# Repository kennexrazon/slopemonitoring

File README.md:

# slopemonitoring
Schematic , Board and SketchUp Files (sch,brd,skp files)

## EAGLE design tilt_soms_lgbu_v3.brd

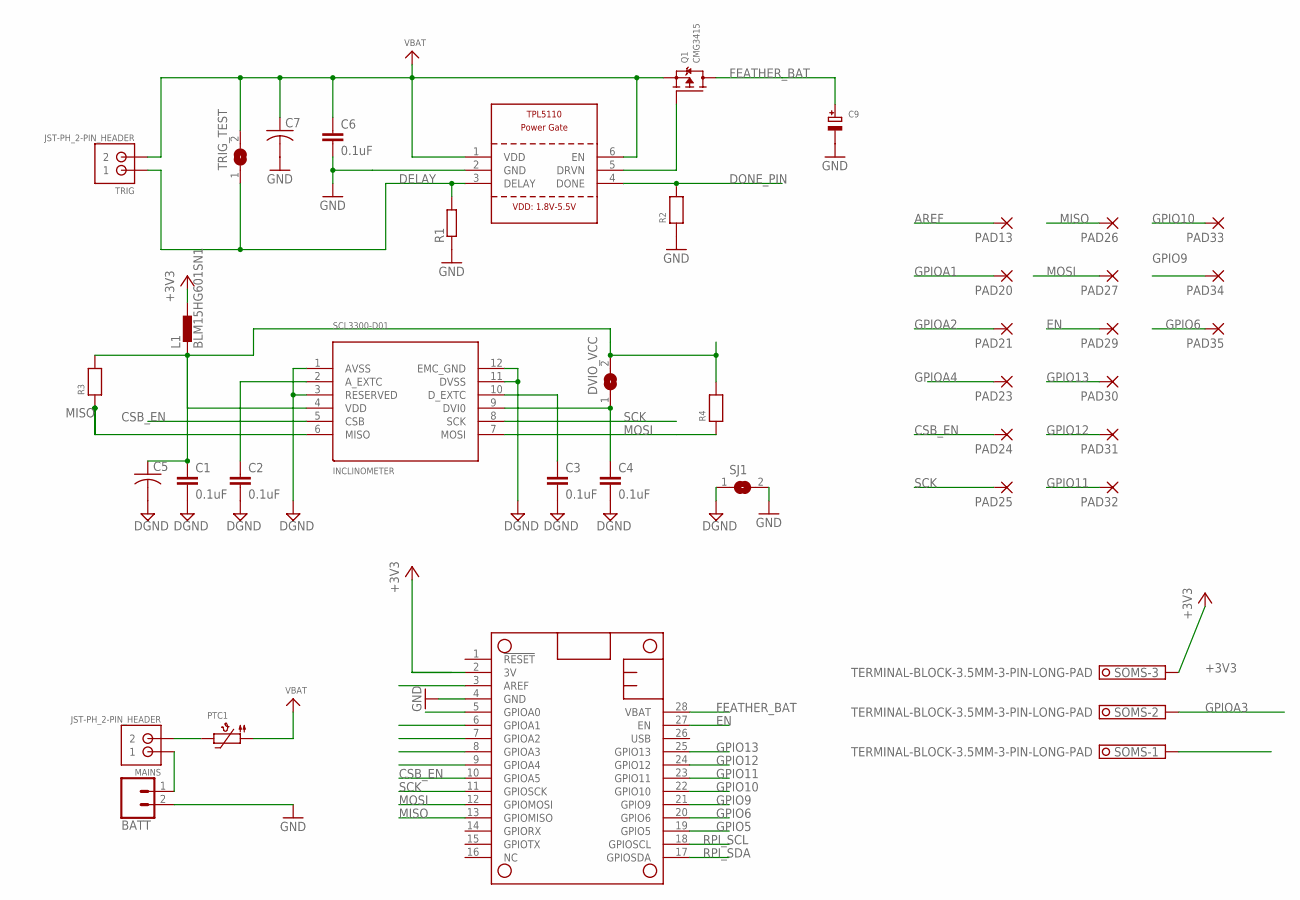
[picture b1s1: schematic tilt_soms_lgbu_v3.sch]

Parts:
BATT: CONN_02POLAR_LOCK; MOLEX-1X2_LOCK
C1, C2, C3, C4, C6: 0.1uF; C0402
C5, C7: C-USC1206K; C1206K
C9: CAP_TANTALUMA/3216_WAVE; EIA3216-18/A-W
DVIO_VCC: SOLDERJUMPER; SOLDERJUMPER_ARROW_NOPASTE
INCLINOMETER: SCL3300-D01
L1: BLM15HG601SN1; 0402
MAINS: JST-PH_2-PIN_HEADER; JST_B2B-PH_HEADER
MS2: FEATHERWINGFEATHERWING_EDC; FEATHERWING_NODIM_HOLES_2
PAD13, PAD20, PAD21, PAD23, PAD24, PAD25, PAD26, PAD27, PAD29, PAD30, PAD31, PAD32, PAD33, PAD34, PAD35: WIREPADSMD1,27-254; SMD1,27-2,54
PTC1: PTC1210
Q1: CMG3415; SOT23-WIDE
R1: R-EU_0207/10; 0207/10
R2, R3, R4: RESISTOR0805; 0805
SJ1: SJ
SOMS: TERMINAL-BLOCK-3.5MM-3-PIN-LONG-PAD; TERMINAL-BLOCK-3-PIN-3.5MM-LONG-PAD
TIMER: TPL5110; SOT23-6
TRIG: JST-PH_2-PIN_HEADER; JST_B2B-PH_HEADER
TRIG_TEST: SOLDERJUMPER; SOLDERJUMPER_ARROW_NOPASTE

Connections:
+3V3: L1.2, MS2.2 (3V), SOMS.3
AREF: MS2.3 (AREF), PAD13.1
CSB_EN: INCLINOMETER.5 (CSB), MS2.10 (GPIOA5), PAD24.1
DELAY: R1.2, TIMER.3 (DELAY), TRIG.P1 (1), TRIG_TEST.1
DGND: C1.2, C2.2, C3.2, C4.2, C5.2, INCLINOMETER.1 (AVSS), INCLINOMETER.3 (RESERVED), INCLINOMETER.11 (DVSS), INCLINOMETER.12 (EMC_GND), SJ1.1
DONE_PIN: MS2.5 (GPIOA0), R2.2, TIMER.4 (DONE)
EN: MS2.27 (EN), PAD29.1
FEATHER_BAT: C9.+, MS2.28 (VBAT), Q1.3 (D)
GND: BATT.2, C6.2, C7.2, C9.-, MS2.4 (GND), R1.1, R2.1, SJ1.2, SOMS.1, TIMER.2 (GND)
GPIO5: MS2.19 (GPIO5)
GPIO6: MS2.20 (GPIO6), PAD35.1
GPIO9: MS2.21 (GPIO9), PAD34.1
GPIO10: MS2.22 (GPIO10), PAD33.1
GPIO11: MS2.23 (GPIO11), PAD32.1
GPIO12: MS2.24 (GPIO12), PAD31.1
GPIO13: MS2.25 (GPIO13), PAD30.1
GPIOA1: MS2.6 (GPIOA1), PAD20.1
GPIOA2: MS2.7 (GPIOA2), PAD21.1
GPIOA3: MS2.8 (GPIOA3), SOMS.2
GPIOA4: MS2.9 (GPIOA4), PAD23.1
MISO: INCLINOMETER.6 (MISO), MS2.13 (GPIOMISO), PAD26.1, R3.1
MOSI: INCLINOMETER.7 (MOSI), MS2.12 (GPIOMOSI), PAD27.1, R4.1
unnamed: C2.1, INCLINOMETER.2 (A_EXTC)
unnamed: C3.1, INCLINOMETER.10 (D_EXTC)
unnamed: BATT.1, MAINS.P1 (1)
unnamed: MAINS.P2 (2), PTC1.P$2 (2)
unnamed: C4.1, DVIO_VCC.1, INCLINOMETER.9 (DVI0)
unnamed: Q1.1 (G), TIMER.5 (DRVN)
unnamed: C1.1, C5.1, DVIO_VCC.2, INCLINOMETER.4 (VDD), L1.1, R3.2, R4.2
RPI_SCL: MS2.18 (GPIOSCL)
RPI_SDA: MS2.17 (GPIOSDA)
SCK: INCLINOMETER.8 (SCK), MS2.11 (GPIOSCK), PAD25.1
VBAT: C6.1, C7.1, PTC1.P$1 (1), Q1.2 (S), TIMER.1 (VDD), TIMER.6 (EN), TRIG.P2 (2), TRIG_TEST.2

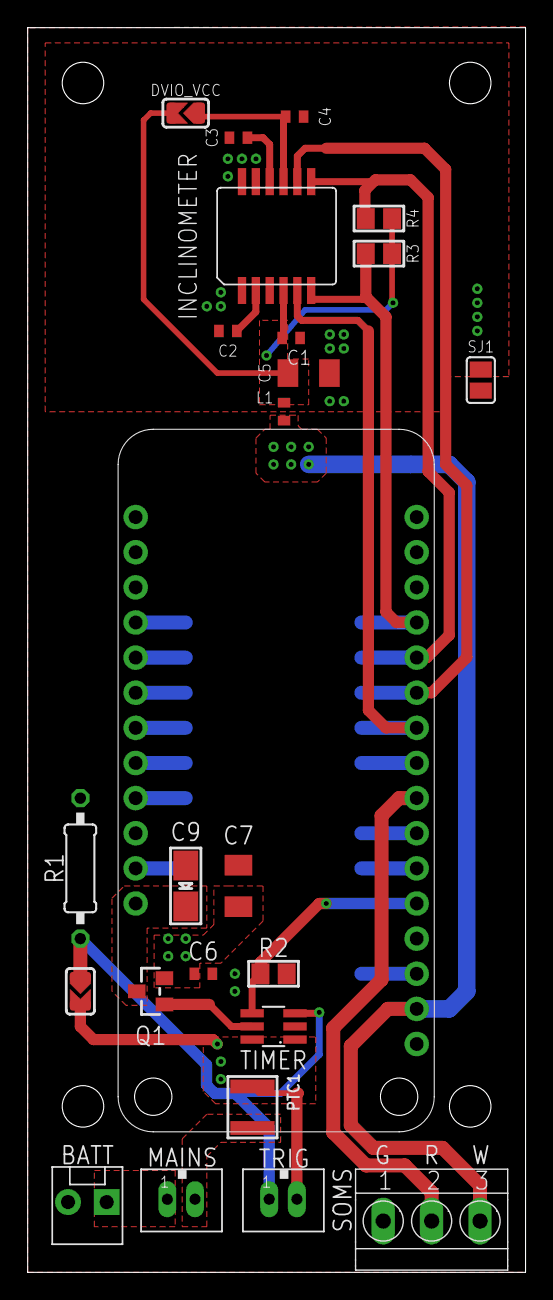
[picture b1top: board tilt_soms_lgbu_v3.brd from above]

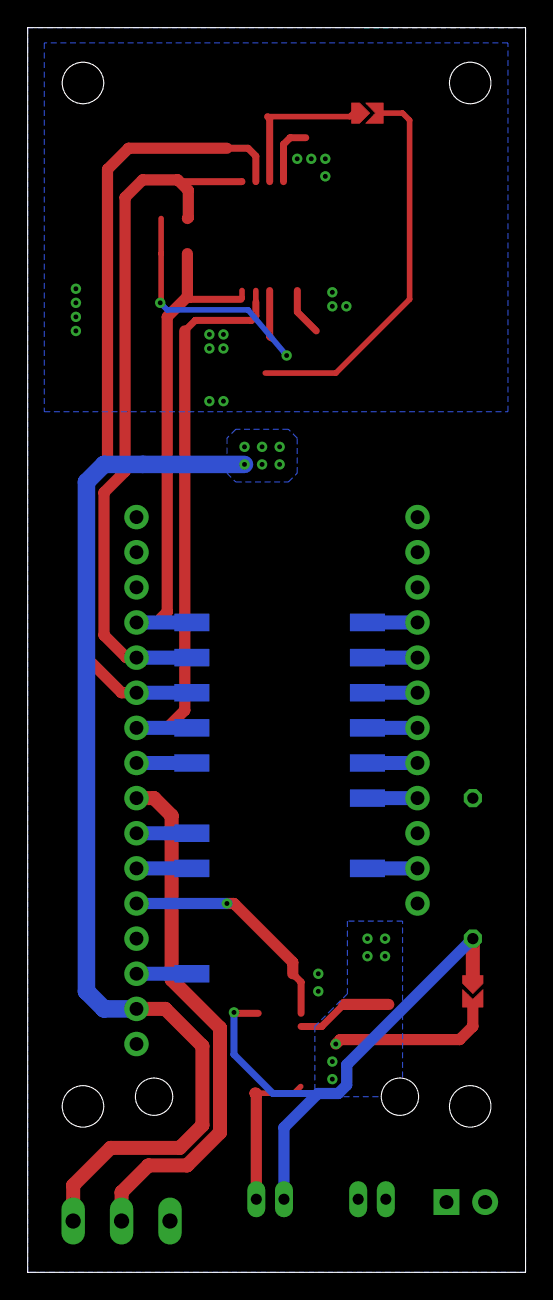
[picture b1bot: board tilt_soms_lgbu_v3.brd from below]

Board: 2 copper layers, 36.0 x 90.0 mm, 40 parts (15 on the bottom side), 30 nets.

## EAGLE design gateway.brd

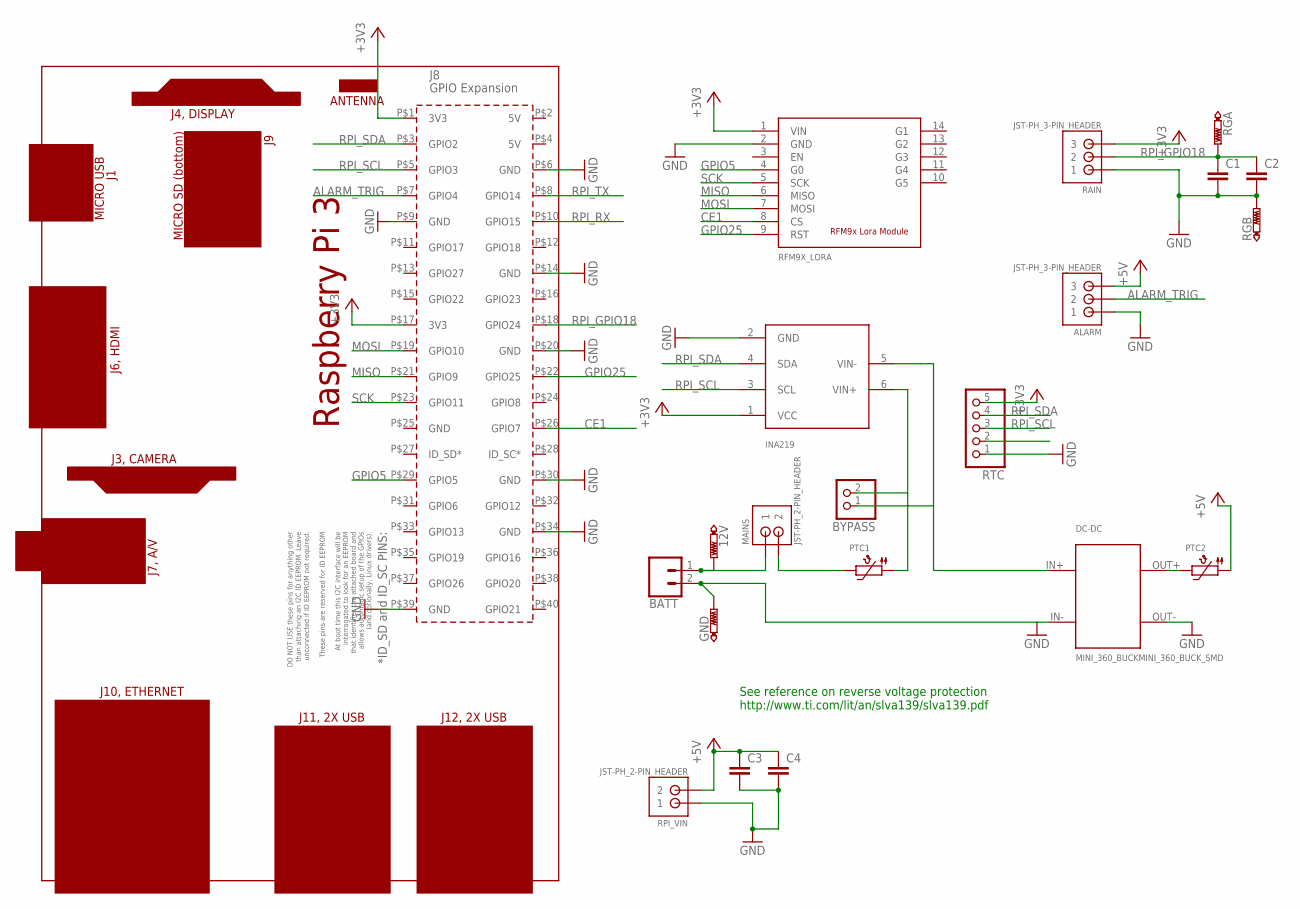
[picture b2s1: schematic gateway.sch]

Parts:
12V: PTR1PAD1-13; P1-13
ALARM: JST-PH_3-PIN_HEADER; JST_B3B-PH_HEADER
BATT: CONN_02POLAR; MOLEX-1X2
BYPASS: PINHD-1X2; 1X02
C1, C2: C-EUC0805; C0805
C3: C-EUC1210; C1210
C4: C-EUC2012; C2012
DC-DC: MINI_360_BUCKMINI_360_BUCK_SMD; MINI_360_BUCK_SMD
GND: PTR1PAD1-13; P1-13
INA219: INA219
MAINS: JST-PH_2-PIN_HEADER; JST_B2B-PH_HEADER
PCB2: RPI3
PTC1: PTC1206; 1206
PTC2: PTC1210
RAIN: JST-PH_3-PIN_HEADER; JST_B3B-PH_HEADER
RFM9X_LORA: RFM9X_MODULE
RGA: PTR1PAD1-13; P1-13
RGB: PTR1PAD1-13; P1-13
RPI_VIN: JST-PH_2-PIN_HEADER; JST_B2B-PH_HEADER
RTC: PINHD-1X5; 1X05

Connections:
+3V3: INA219.1 (VCC), PCB2.P$1 (3V3), PCB2.P$17 (3V3), RAIN.P3 (3), RFM9X_LORA.1 (VIN), RTC.5
+5V: ALARM.P3 (3), C3.1, C4.1, PTC2.P$1 (1), RPI_VIN.P2 (2)
ALARM_TRIG: ALARM.P2 (2), PCB2.P$7 (GPIO4)
CE1: PCB2.P$26 (GPIO7), RFM9X_LORA.8 (CS)
GND: ALARM.P1 (1), BATT.2, C1.2, C2.2, C3.2, C4.2, DC-DC.IN- (VIN-), DC-DC.OUT- (VOUT-), GND.TP, INA219.2 (GND), PCB2.P$6 (GND), PCB2.P$9 (GND), PCB2.P$14 (GND), PCB2.P$20 (GND), PCB2.P$30 (GND), PCB2.P$34 (GND), PCB2.P$39 (GND), RAIN.P1 (1), RFM9X_LORA.2 (GND), RGB.TP, RPI_VIN.P1 (1), RTC.1
GPIO5: PCB2.P$29 (GPIO5), RFM9X_LORA.4 (G0)
GPIO25: PCB2.P$22 (GPIO25), RFM9X_LORA.9 (RST)
MISO: PCB2.P$21 (GPIO9), RFM9X_LORA.6 (MISO)
MOSI: PCB2.P$19 (GPIO10), RFM9X_LORA.7 (MOSI)
unnamed: 12V.TP, BATT.1, MAINS.P1 (1)
unnamed: MAINS.P2 (2), PTC1.2
unnamed: BYPASS.1, DC-DC.IN+ (VIN+), INA219.5 (VIN-)
unnamed: BYPASS.2, INA219.6 (VIN+), PTC1.1
unnamed: DC-DC.OUT+ (VOUT+), PTC2.P$2 (2)
RPI_GPIO18: C1.1, C2.1, PCB2.P$18 (GPIO24), RAIN.P2 (2), RGA.TP
RPI_RX: PCB2.P$10 (GPIO15)
RPI_SCL: INA219.3 (SCL), PCB2.P$5 (GPIO3), RTC.3
RPI_SDA: INA219.4 (SDA), PCB2.P$3 (GPIO2), RTC.4
RPI_TX: PCB2.P$8 (GPIO14)
SCK: PCB2.P$23 (GPIO11), RFM9X_LORA.5 (SCK)

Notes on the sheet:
See reference on reverse voltage protection http://www.ti.com/lit/an/slva139/slva139.pdf

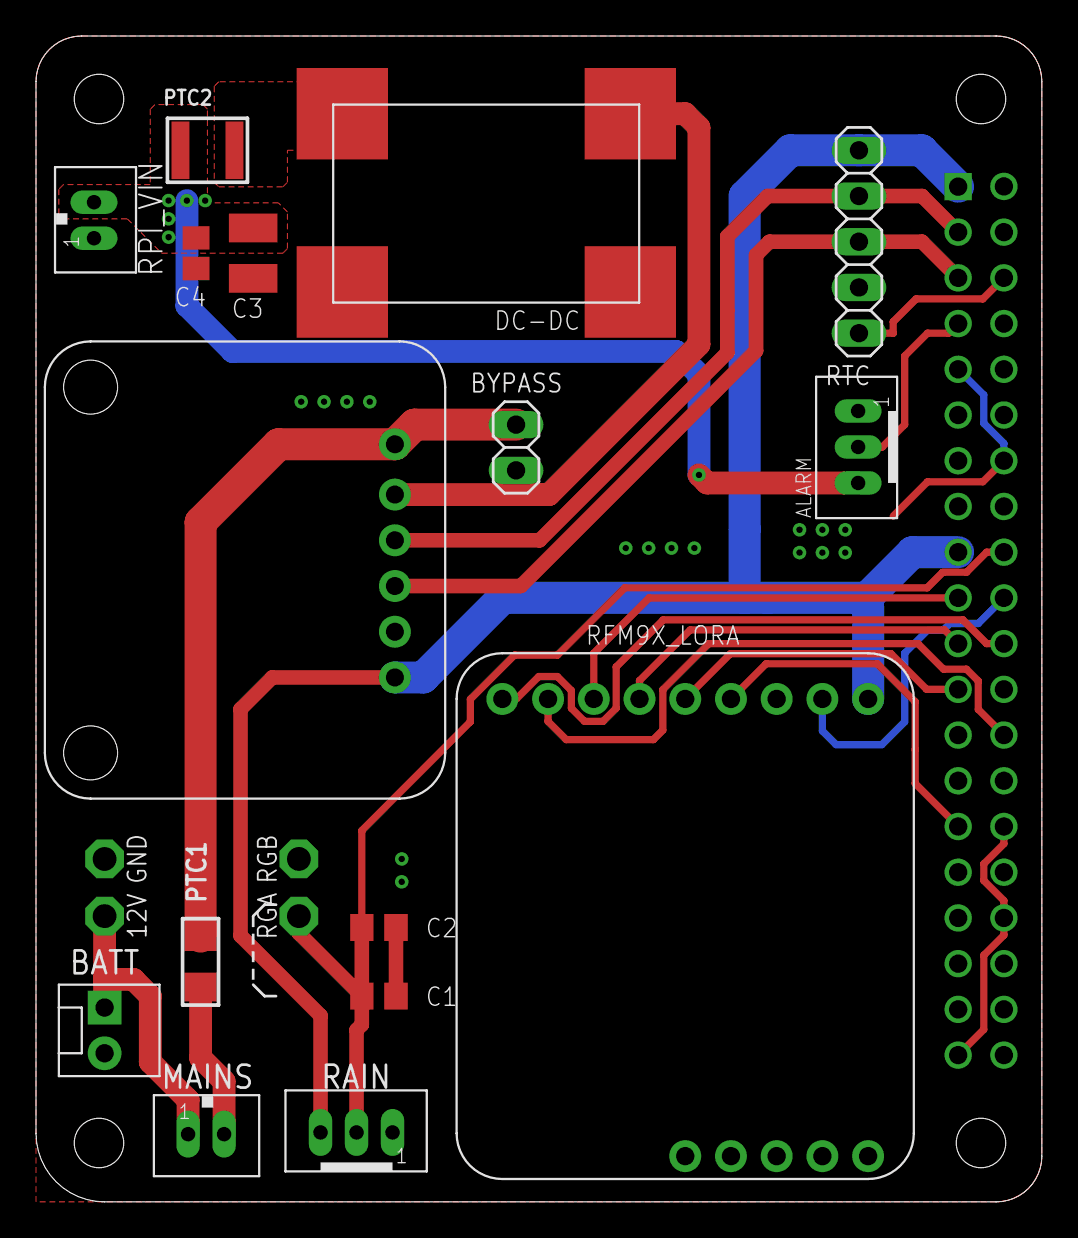
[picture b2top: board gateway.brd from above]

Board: 2 copper layers, 55.9 x 64.8 mm, 21 parts (0 on the bottom side), 18 nets.

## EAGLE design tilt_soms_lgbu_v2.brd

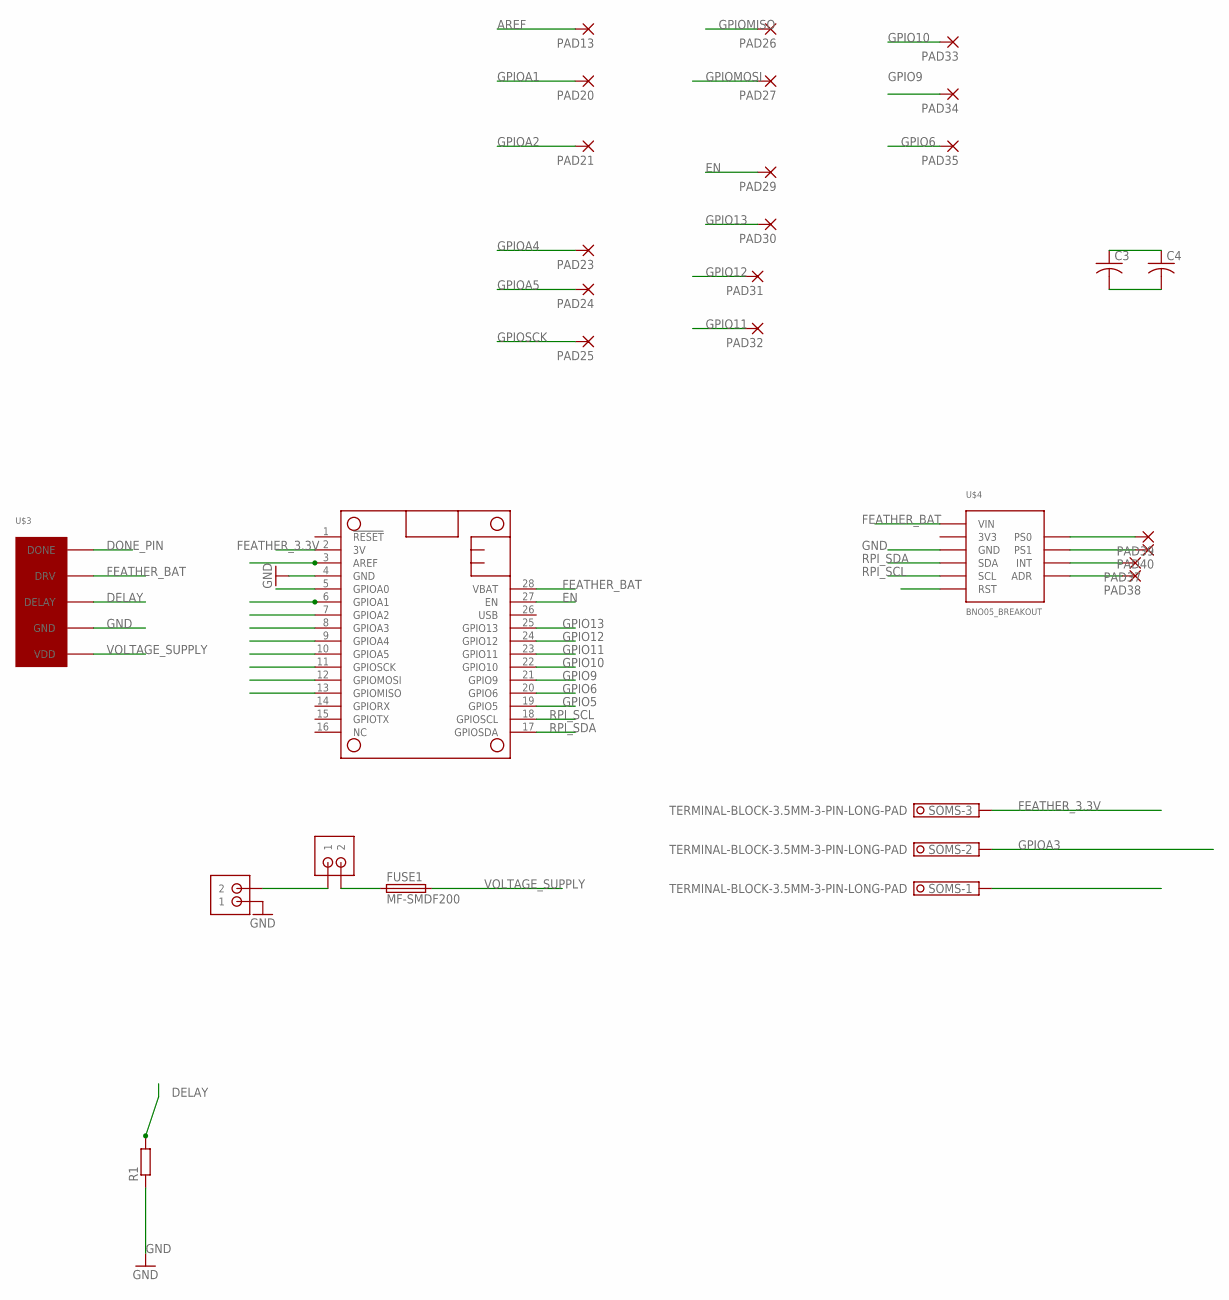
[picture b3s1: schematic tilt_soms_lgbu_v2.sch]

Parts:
BATT: JST-PH_2-PIN_HEADER; JST_B2B-PH_HEADER
C3, C4: C-USC1812; C1812
FUSE1: MF-SMDF200; MF-SMDF050
MAIN_SWITCH: JST-PH_2-PIN_HEADER; JST_B2B-PH_HEADER
MS1: FEATHERWING_NODIM; FEATHERWING_DIM
PAD13, PAD20, PAD21, PAD23, PAD24, PAD25, PAD26, PAD27, PAD29, PAD30, PAD31, PAD32, PAD33, PAD34, PAD35, PAD37, PAD38, PAD39, PAD40: WIREPADSMD1,27-254; SMD1,27-2,54
R1: R-EU_0309/12; 0309/12
SOMS: TERMINAL-BLOCK-3.5MM-3-PIN-LONG-PAD; TERMINAL-BLOCK-3-PIN-3.5MM-LONG-PAD
U$3: TPL5110_BREAKOUT
U$4: BNO05_BREAKOUT

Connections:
AREF: MS1.3 (AREF), PAD13.1
DELAY: R1.2, U$3.DELAY
DONE_PIN: MS1.5 (GPIOA0), U$3.DONE
EN: MS1.27 (EN), PAD29.1
FEATHER_3.3V: MS1.2 (3V), SOMS.3
FEATHER_BAT: MS1.28 (VBAT), U$3.DRV, U$4.VIN
GND: BATT.P1 (1), C3.2, C4.2, MS1.4 (GND), R1.1, SOMS.1, U$3.GND, U$4.GND
GPIO5: MS1.19 (GPIO5), U$4.RST
GPIO6: MS1.20 (GPIO6), PAD35.1
GPIO9: MS1.21 (GPIO9), PAD34.1
GPIO10: MS1.22 (GPIO10), PAD33.1
GPIO11: MS1.23 (GPIO11), PAD32.1
GPIO12: MS1.24 (GPIO12), PAD31.1
GPIO13: MS1.25 (GPIO13), PAD30.1
GPIOA1: MS1.6 (GPIOA1), PAD20.1
GPIOA2: MS1.7 (GPIOA2), PAD21.1
GPIOA3: MS1.8 (GPIOA3), SOMS.2
GPIOA4: MS1.9 (GPIOA4), PAD23.1
GPIOA5: MS1.10 (GPIOA5), PAD24.1
GPIOMISO: MS1.13 (GPIOMISO), PAD26.1
GPIOMOSI: MS1.12 (GPIOMOSI), PAD27.1
GPIOSCK: MS1.11 (GPIOSCK), PAD25.1
unnamed: PAD37.1, U$4.INT
unnamed: BATT.P2 (2), MAIN_SWITCH.P1 (1)
unnamed: FUSE1.1, MAIN_SWITCH.P2 (2)
unnamed: PAD38.1, U$4.ADR
unnamed: PAD39.1, U$4.PS0
unnamed: PAD40.1, U$4.PS1
RPI_SCL: MS1.18 (GPIOSCL), U$4.SCL
RPI_SDA: MS1.17 (GPIOSDA), U$4.SDA
VOLTAGE_SUPPLY: C3.1, C4.1, FUSE1.2, U$3.VDD

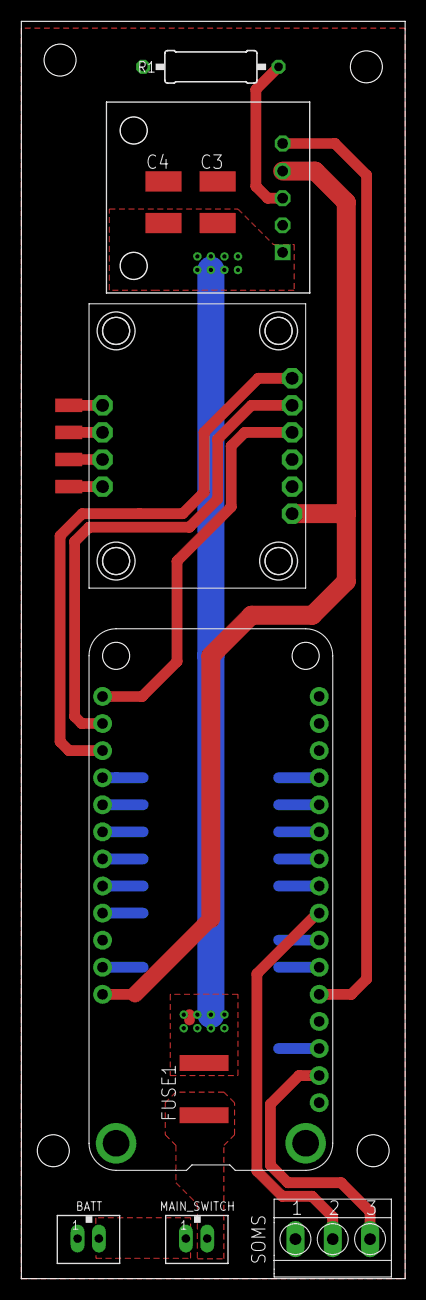
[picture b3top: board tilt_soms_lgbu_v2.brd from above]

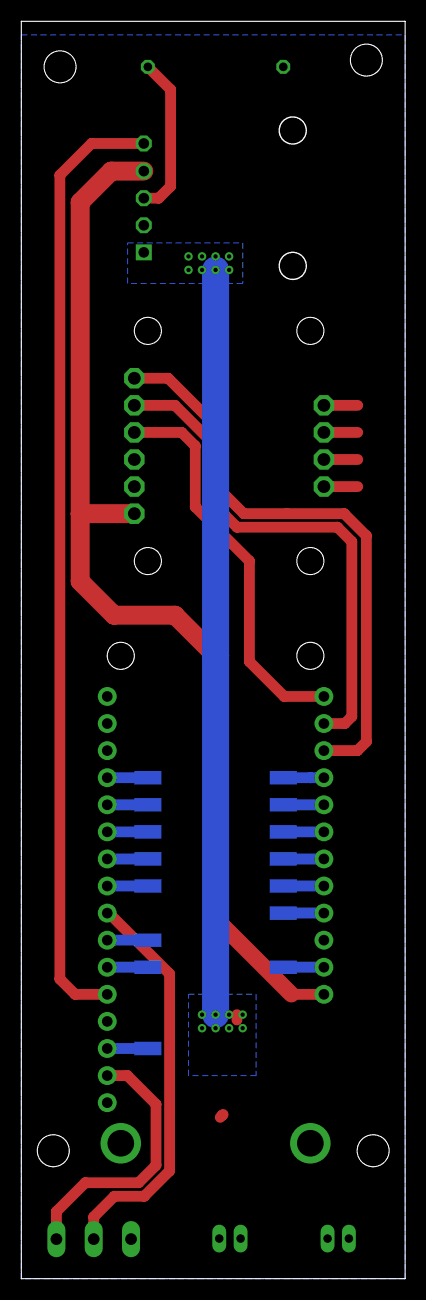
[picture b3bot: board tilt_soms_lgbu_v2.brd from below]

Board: 2 copper layers, 35.9 x 117.8 mm, 29 parts (15 on the bottom side), 31 nets.

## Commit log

2018-07-22 tp5100 board as component added
2018-07-23 correction to tp5100 package
2018-07-23 added mini_360_buck
2018-07-25 added tpl5110 breakout
2018-07-26 changed the pad sizes of a few module packages
2018-07-26 added gateway.brd and gateway.sch
2018-07-27 added solar charge controller and delay timer. still need edits on the supply line of feather board.
2018-07-28 added another rtc for feather ( tilt only config )
    added the bno05_breakout footprint
2018-07-29 finished routing
2018-08-01 added pads to the microcontrollers ( feather and pi )
2018-08-01 added more fuse for more protection
2018-08-01 added a 2mm tplace line around board.
    changed rain header to 1.5mm pitch
2018-08-02 fixed all drc errors
2018-08-02 forgot to commit brd files
2018-08-02 changed bno05 vin / 3.3V connection
2018-08-02 added reset for IMU
2018-08-02 added header for main_switch
2018-08-03 added soms
2018-10-06 slim tilt board first layout
2018-12-01 Added a v2 for the tilt_soms_lgbu board (tilt_soms_lgbu_v2)
    Primary changes:
    Placed all components on top layer including the con-wago connectors.
2018-12-01 Reversed board. Snap to mills grid.
2019-03-19 no dip switch
2019-06-20 edc modules changes - scl3300-d01 - timer breakout - ina219
2019-06-20 new version of tilt board
2019-06-20 fixed unrouted trace
2019-06-20 edc modules - larger pad size for dcdc gateway - right package for capacitor and fuse tilt board - no more timer module, embedded design, right packages for caps and fuse
2019-07-11 added used edited libraries
2019-07-11 ferrite bead, pull ups, standard battery header
2019-07-11 new gateway versions
2019-07-18 few gateway revisions
2019-07-18 tilt_soms_lgbu_v3.brd minor changes
2019-08-02 lengthen scl3300 pads, isolated pads for axel, all supply goes through a ferrite bead
2019-08-02 longer pads for scl3300
2019-08-03 *changed the pad length of scl3300-do1 from 1.48 x 0.61 to 1.96 x 0.61
2019-08-03 *changed tpl5110 pad length from 0.9 to 1.7

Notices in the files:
parts and their libraries:
microbuilder: This work is placed in the public domain, and may be freely used for commercial and non-commercial work with the following conditions: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
SparkFun-Connectors: Licensing: Creative Commons ShareAlike 4.0 International - https://creativecommons.org/licenses/by-sa/4.0
